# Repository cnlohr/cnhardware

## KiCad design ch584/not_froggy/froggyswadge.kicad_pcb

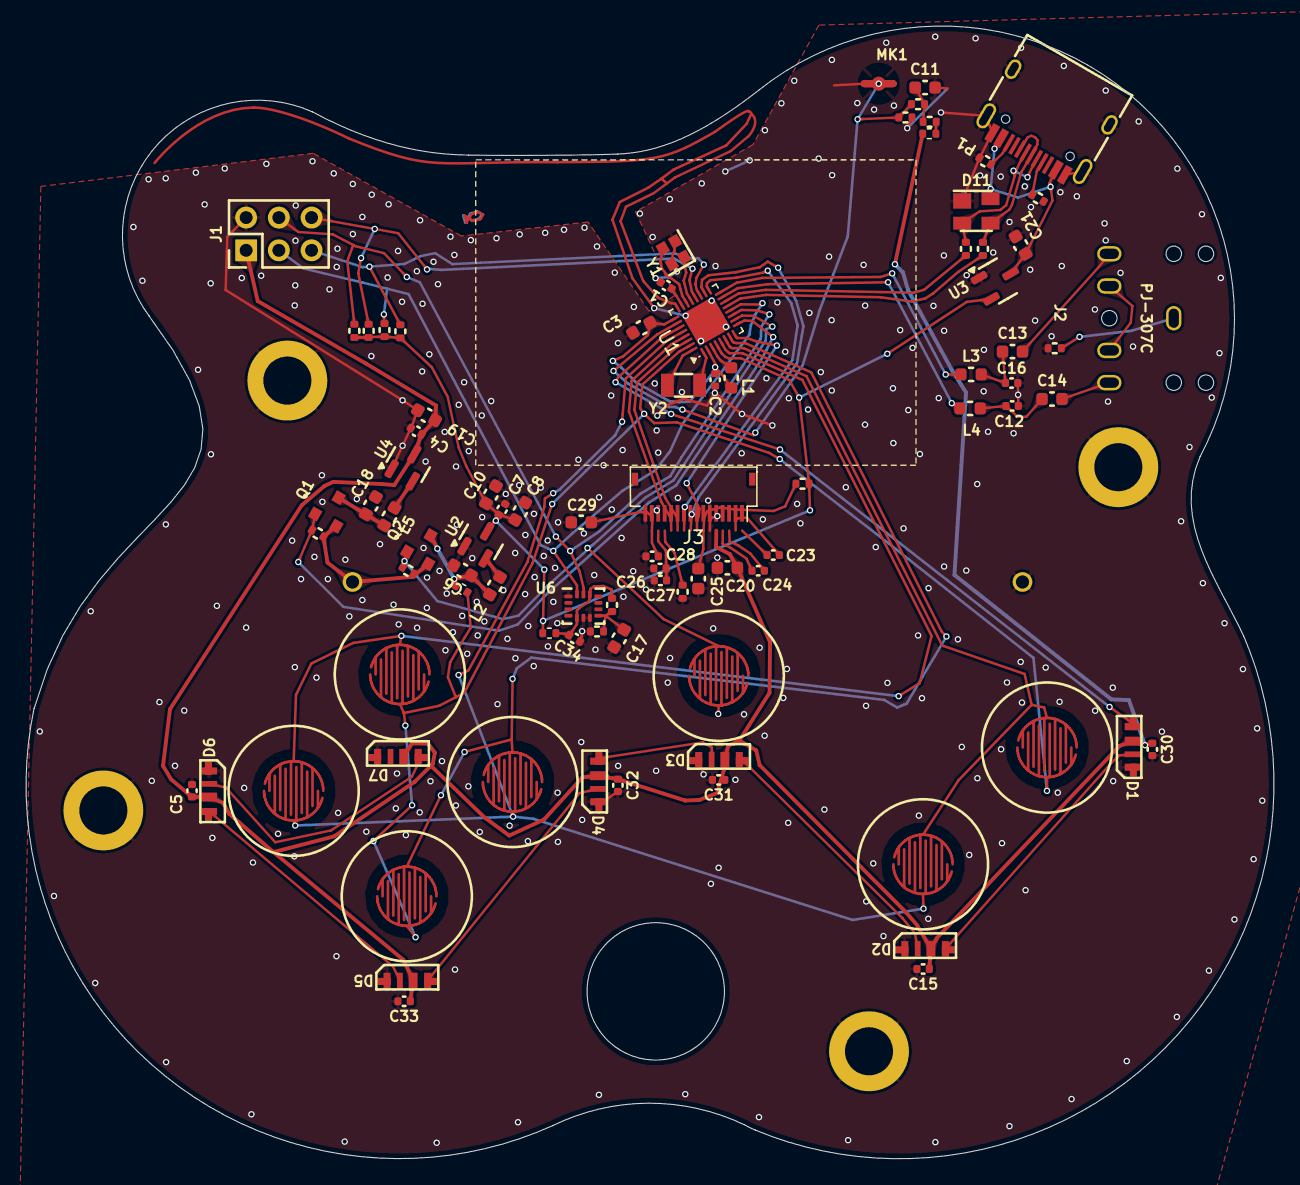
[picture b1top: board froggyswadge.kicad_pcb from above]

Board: 2 copper layers, 96.8 x 87.9 mm, 92 parts (1 on the bottom side), 66 nets.

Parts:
BT1: Battery; 2460
C1, C4, C5, C12, C15, C16, C23, C24, C26, C27, C28, C30, C31, C32, C33, C34: 1μF; C_0402_1005Metric
C2, C7: 100nF; C_0402_1005Metric
C3, C6, C8, C10, C11, C13, C14, C17, C18, C19, C20, C21, C25, C29: 10μF; C_0603_1608Metric
C9, C22: 4.7nF; R_0402_1005Metric_COMPACT
D1, D2, D3, D4, D5, D6, D7: SK6812-SIDE-A; SK6812_SIDE_2
D11: SP0503BAHT; SOT-143
J1: SAO; PinHeader_2x03_P2.54mm_Vertical
J2: PJ-307C
J3: RB130-2864KSWXG22; FPC-16-P0.50mm-HC-FPC-05-09-16RLTAG-TOP-AND-BOTTOM
J4, J5, J6, J7: MOUNT; SMTSO20xx
L1, L2, L3, L4, L5: 10uH; L_0603_1608Metric
MK1: 56db; INGHAi_MIC_GMI4013S-2C58DB
P1: USB_C_Plug_USB2.0; USB_C_Receptacle_HRO_TYPE-C-31-M-12
Q1, Q2: PMOS; SOT-23
R1, R7, R8, R11, R12, R27, R28: 5.1kΩ; R_0402_1005Metric_COMPACT
R2, R3, R6, R13, R14: 33Ω; R_0402_1005Metric_COMPACT
R4, R5: 1MΩ; R_0402_1005Metric_COMPACT
R9: IMUSHUNT; R_0402_1005Metric_COMPACT
R10, R16: 560kΩ; R_0402_1005Metric_COMPACT
R15: OLEDSHUNT; R_0402_1005Metric_COMPACT
R17: MICSHUNT; R_0402_1005Metric_COMPACT
SW1, SW2, SW3, SW4, SW5, SW6, SW7: TS-1187A-B-A-B; BTC007_Button_Silicone
U1: CH584F; VQFN-32-1EP_4x4mm_P0.4mm_EP2.8x2.8mm
U2: SM5701_2.2V; SOT-23
U3: XC6206PxxxMR; SOT-23-3
U4: XT1861B332MR-G; SOT-23
U6: LSM6DSL; LGA-14_3x2.5mm_P0.5mm_LayoutBorder3x4y
Y1: 32MHz; Crystal_SMD_2016-4Pin_2.0x1.6mm
Y2: 32.768kHz; Crystal_SMD_3215-2Pin_3.2x1.5mm

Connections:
+2V2: C7.1, C8.1, C10.1, R7.1, R8.1, R9.1, R11.1, R12.1, R15.2, U1.4 (VIO/DD33), U2.3 (OUT), U3.2 (VO)
+3V3: C4.1, C5.1, C15.1, C19.1, C20.1, C30.1, C31.1, C32.1, C33.1, D1.2 (VDD), D2.2 (VDD), D3.2 (VDD), D4.2 (VDD), D5.2 (VDD), D6.2 (VDD), D7.2 (VDD), J1.1, J3.5, R17.2, U4.3 (OUT)
AUDIOM: L4.1, U1.15 (B7)
AUDIOP: L3.1, U1.16 (B6)
B0: SW1.1 (A), SW4.1 (A), U1.5 (B9)
B1: SW2.1 (A), SW5.1 (A), U1.6 (B8)
B2: SW3.1 (A), SW6.1 (A), U1.7 (B17)
BARA: R10.1, SW1.2 (B), SW2.2 (B), SW3.2 (B), U1.31 (PA12)
BARB: SW4.2 (B), SW5.2 (B), SW6.2 (B), U1.28 (PA15)
BATT: BT1.1 (+), Q1.2 (S), Q2.2 (S), R4.1, R5.1
BATTLX22: L2.2, U2.2 (LX)
BATTLX33: L5.2, U4.2 (LX)
BATTMID22: C6.1, L2.1, Q2.3 (D), R10.2
BATTMID33: C18.1, L5.1, Q1.3 (D)
CC1: P1.A5 (CC1), R28.2
CC2: P1.B5 (CC2), R27.2
GND: BT1.2 (-), C1.2, C2.2, C3.2, C4.2, C5.2, C6.2, C7.2, C8.2, C9.1, C10.2, C11.2, C12.2, C15.2, C16.2, C17.1, C18.2, C19.2, C20.2, C21.2, C22.1, C25.2, C26.2, C27.2, C28.2, C29.2, C30.2, C31.2, C32.2, C33.2, C34.1, D1.4 (GND), D2.4 (GND), D3.4 (GND), D4.4 (GND), D5.4 (GND), D6.4 (GND), D7.4 (GND), D11.1 (A), J1.2, J3.6, J3.16, J4.1, J5.1, J6.1, J7.1, MK1.1 (-), P1.A1_B12 (GND), P1.A12_B1 (GND), P1.S1 (SHIELD), R3.2, R16.2, R27.1, R28.1, SW7.2 (B), U1.24 (ANT), U1.33 (F), U2.1 (GND), U3.1 (GND), U4.1 (GND), U6.1 (SA0), U6.6 (GND), U6.7 (GND), Y1.2, Y1.4
LED: D1.1 (IN), U1.27 (PA5)
MIC: C9.2, MK1.2 (+), R1.1, U1.26 (PA4)
unnamed: C11.1, R1.2, R2.1
unnamed: C12.1, C14.1, L4.2
unnamed: C13.1, C16.1, L3.2
unnamed: C13.2, J2.5
unnamed: C14.2, J2.2
unnamed: D1.3 (OUT), D2.1 (IN)
unnamed: D2.3 (OUT), D3.1 (IN)
unnamed: D3.3 (OUT), D4.1 (IN)
unnamed: D4.3 (OUT), D5.1 (IN)
unnamed: D5.3 (OUT), D6.1 (IN)
unnamed: D6.3 (OUT), D7.1 (IN)
unnamed: J2.1, R3.1
unnamed: J2.3, J2.4
unnamed: C23.2, J3.1
unnamed: C23.1, J3.2
unnamed: C24.2, J3.3
unnamed: C24.1, J3.4
unnamed: C25.1, J3.7, R15.1
unnamed: J3.13, R16.1
unnamed: C26.1, C27.1, J3.14
unnamed: C28.1, C29.1, J3.15
unnamed: D11.2 (K), P1.A7 (DN1), P1.B7 (DN2), R14.2
unnamed: D11.3 (K), P1.A6 (DP1), P1.B6 (DP2), R13.2
unnamed: R2.2, R17.1
unnamed: U1.1 (A10), Y2.1
unnamed: U1.32 (PA11), Y2.2
unnamed: C1.1, U1.23 (VINTA)
unnamed: L1.2, U1.3 (VSW)
unnamed: U1.22 (X32MI), Y1.3
unnamed: U1.21 (X32MO), Y1.1
unnamed: C34.2, R6.1, R9.2, U6.5 (VDDIO), U6.12 (CS)
unnamed: C17.2, C22.2, R6.2, U6.8 (VDD)
OLEDCS: J3.8, U1.8 (B16)
OLEDDC: J3.10, U1.17 (B5)
OLEDMOSI: J3.12, U1.29 (PA14)
OLEDRST: J3.9, U1.18 (B4)
OLEDSCK: J3.11, U1.30 (PA13)
PGM_TCK: Q1.1 (G), R4.2, U1.9 (B15)
PGM_TIO: Q2.1 (G), R5.2, SW7.1 (A), U1.10 (B14)
SAOG1: J1.5, R12.2, U1.19 (B23)
SAOG2: J1.6, R11.2, U1.20 (B22)
SCL_SAO: J1.4, R8.2, U1.11 (B13), U6.13 (SCL)
SDA_SAO: J1.3, R7.2, U1.12 (B12), U6.14 (SDA)
USB_D+: R13.1, U1.13 (B11)
USB_D-: R14.1, U1.14 (B10)
VBUS: C21.1, D11.4 (K), P1.A4_B9 (VBUS), P1.A9_B4 (VBUS), U3.3 (VI)
VCIA: C2.1, C3.1, L1.1, U1.2 (VDCID), U1.25 (VCIA)

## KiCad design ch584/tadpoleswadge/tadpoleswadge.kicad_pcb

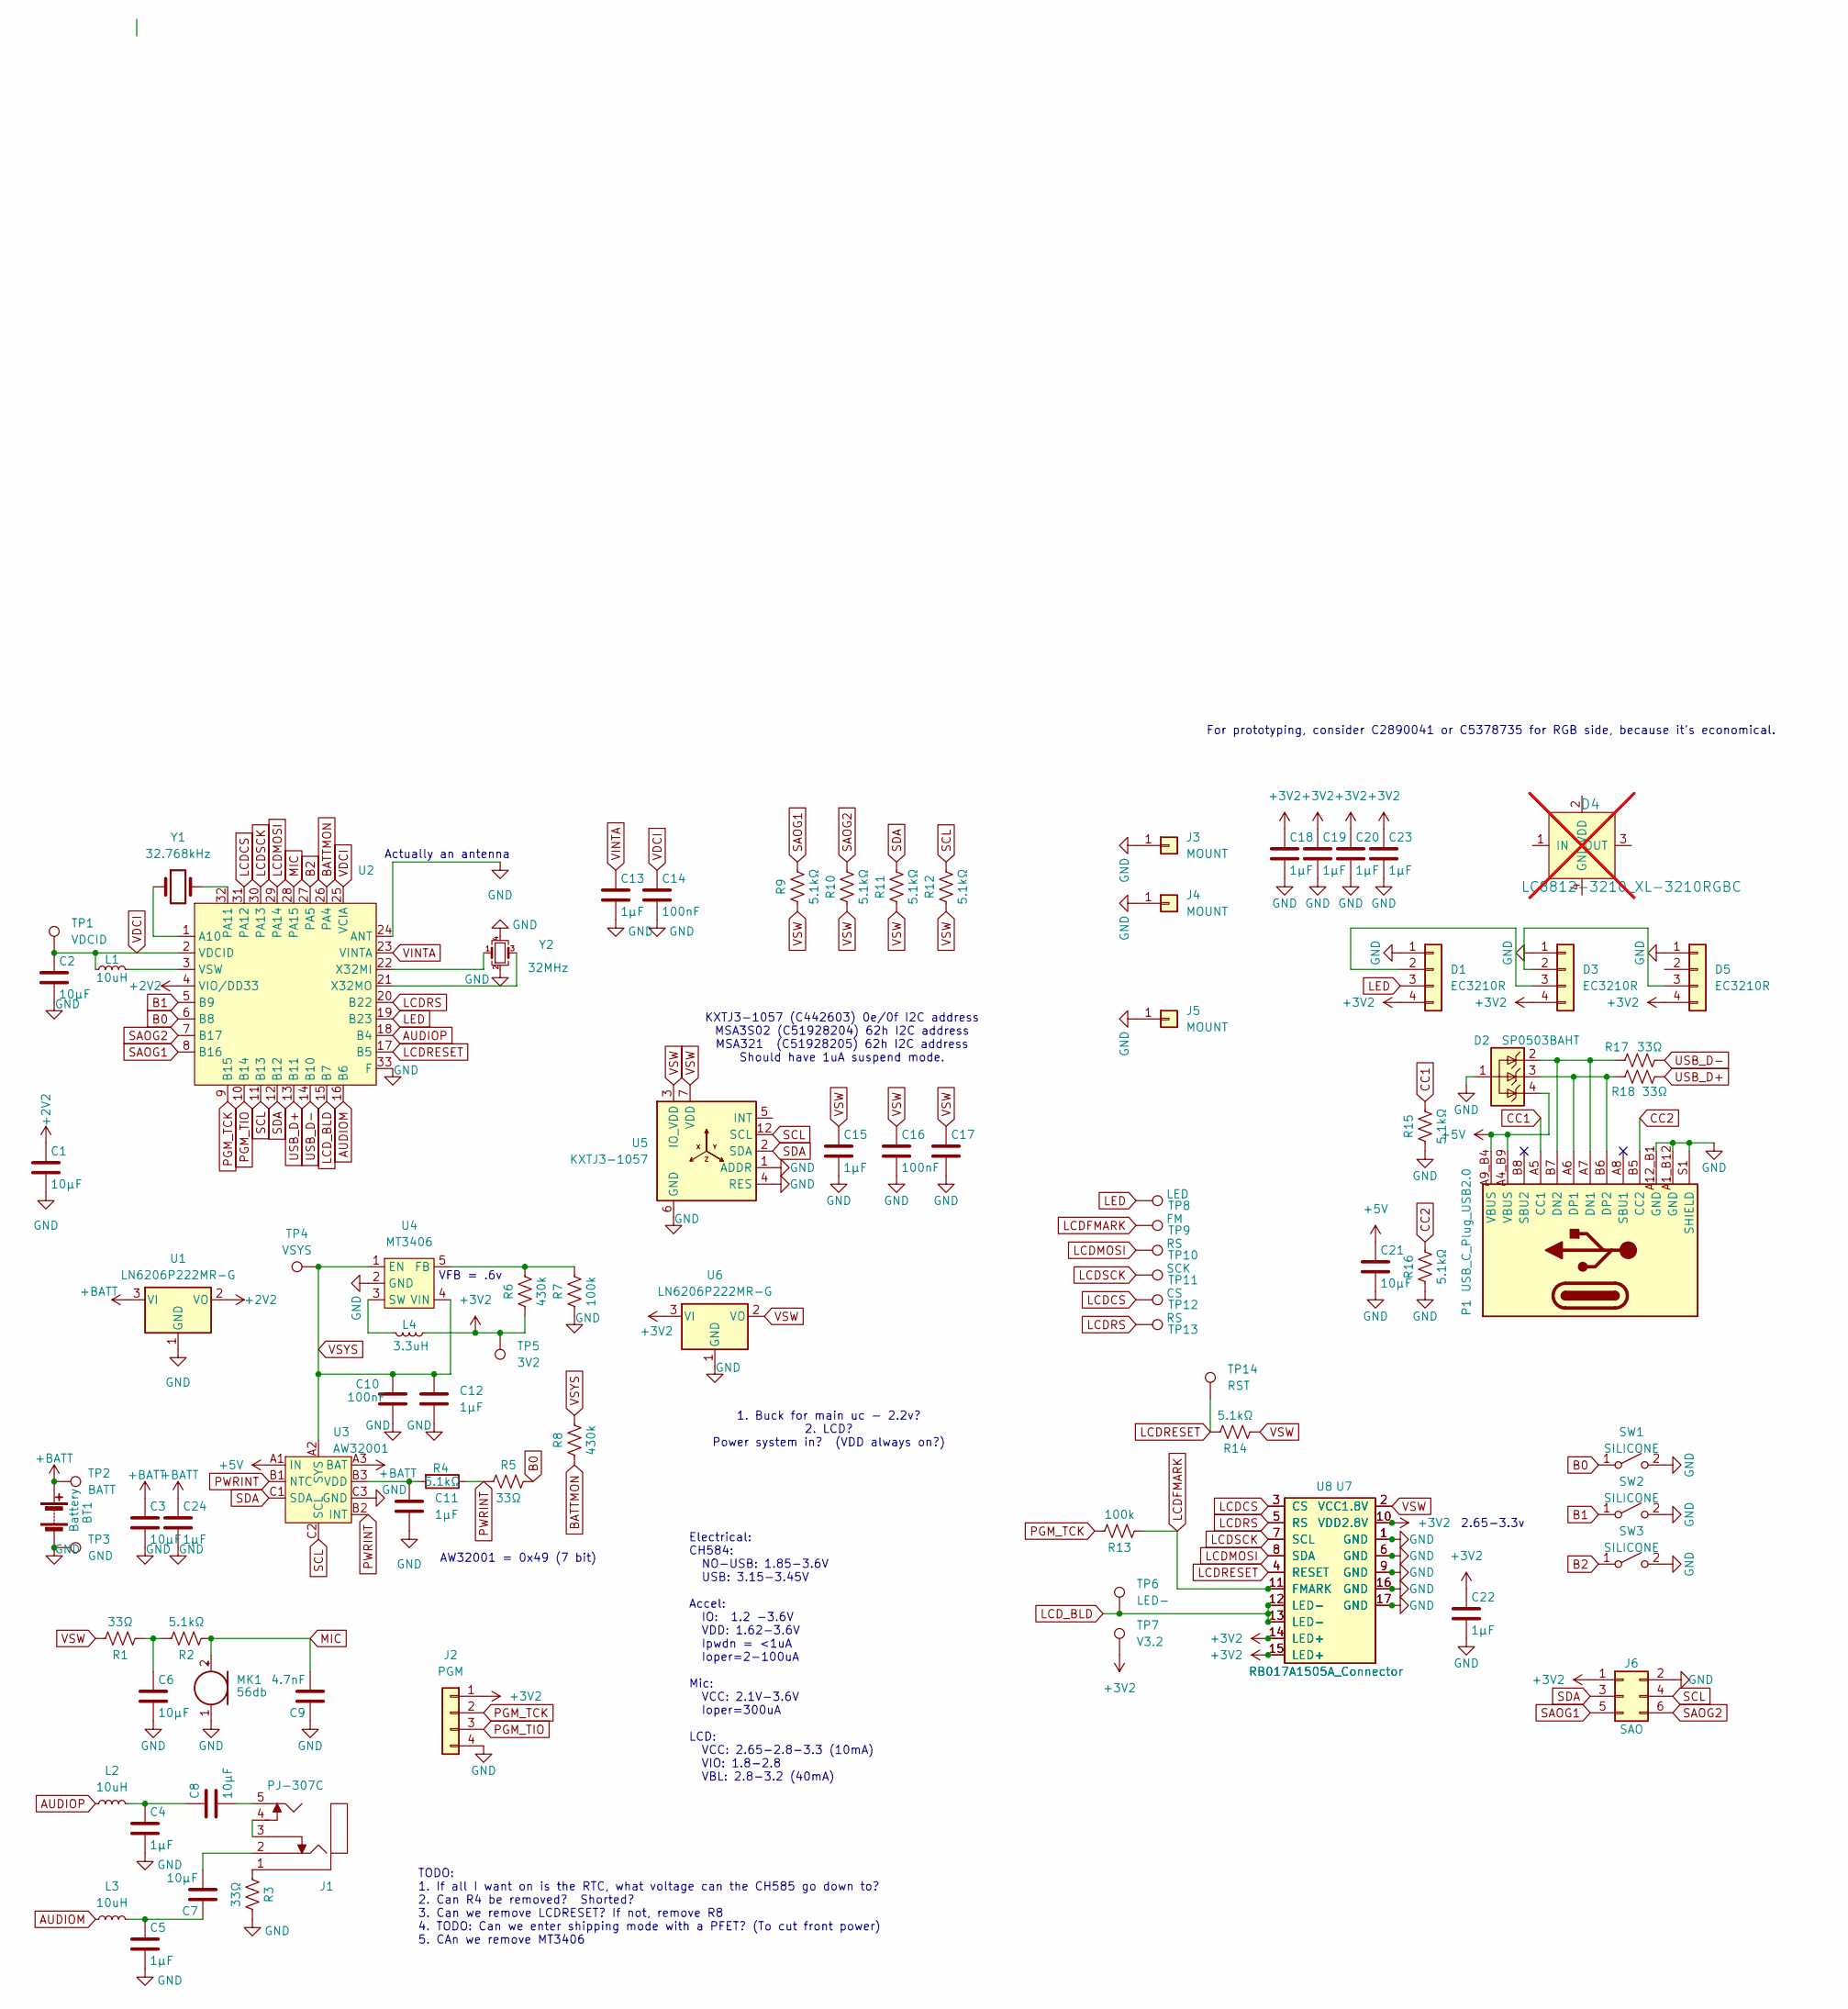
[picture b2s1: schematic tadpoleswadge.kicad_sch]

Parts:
BT1: Battery; 2460
C1, C2, C3, C6, C7, C8, C17, C21: 10μF; C_0603_1608Metric; LCSC C19702
C4, C5, C11, C12, C13, C15, C18, C19, C20, C22, C23, C24: 1μF; C_0402_1005Metric; LCSC C52923
C9: 4.7nF; R_0402_1005Metric_COMPACT; LCSC C1538
C10, C14, C16: 100nF; C_0402_1005Metric; LCSC C1525
D1, D3, D5: EC3210R; EC3210R-OPSCO-RGB-LED; LCSC C2890041
D2: SP0503BAHT; SOT-143; Digikey F2715CT-ND
D4: LC8812-3210_XL-3210RGBC; Digikey 1528-4691-ND; not fitted
J1: PJ-307C; LCSC C16684
J2: PGM; PinHeader_1x04_P2.54mm_Vertical
J3, J4, J5: MOUNT; SMTSO20xx; LCSC C2916318
J6: SAO; PinSocket_2x03_P2.54mm_Vertical; LCSC C92272
L1, L2, L3: 10uH; L_0603_1608Metric; LCSC C307750
L4: 3.3uH; L_0805_2012Metric; LCSC C394958
MK1: 56db; INGHAi_MIC_GMI4013S-2C58DB; LCSC C529869
P1: USB_C_Plug_USB2.0; USB_C_Receptacle_HRO_TYPE-C-31-M-12; LCSC C2765186
R1, R3, R5, R17, R18: 33Ω; R_0402_1005Metric_COMPACT; LCSC C25105
R2, R4, R9, R10, R11, R12, R14, R15, R16: 5.1kΩ; R_0402_1005Metric_COMPACT; LCSC C25905
R6, R8: 430k; R_0402_1005Metric_COMPACT; LCSC C25786
R7, R13: 100k; R_0402_1005Metric_COMPACT; LCSC C25741
SW1, SW2, SW3: SILICONE; BTC007_Button_Silicone
TP1: VDCID; TestPoint_Pad_D1.0mm
TP2: BATT; TestPoint_Pad_D1.0mm
TP3: GND; TestPoint_Pad_D1.0mm
TP4: VSYS; TestPoint_Pad_D1.0mm
TP5: 3V2; TestPoint_Pad_D1.0mm
TP6: LED-; TestPoint_Pad_D1.0mm
TP7: V3.2; TestPoint_Pad_D1.0mm
TP8: LED; TestPoint_Pad_D1.0mm
TP9: FM; TestPoint_Pad_D1.0mm
TP10, TP13: RS; TestPoint_Pad_D1.0mm
TP11: SCK; TestPoint_Pad_D1.0mm
TP12: CS; TestPoint_Pad_D1.0mm
TP14: RST; TestPoint_Pad_D1.0mm
U1, U6: LN6206P222MR-G; SOT-23; LCSC C3008044
U2: VQFN-32-1EP_4x4mm_P0.4mm_EP2.8x2.8mm; LCSC C42381468
U3: AW32001; WLCSP-9-P0.5mm; LCSC C5125890
U4: MT3406; SOT-23-5; LCSC C22462728
U5: KXTJ3-1057; Kionix_LGA-12_2x2mm_P0.5mm_LayoutBorder2x4y; LCSC C51928204
U7: RB017A1505A_Connector; HCTL HC-FPC-03-10-15RLTAG-TUCKED; Digikey A141392TR-ND
U8: RB017A1505A_Connector; 0.3K-HX-15PWB-LCD-CONNECTOR-TOP; LCSC C2919525
Y1: 32.768kHz; Crystal_SMD_3215-2Pin_3.2x1.5mm; LCSC C7294751
Y2: 32MHz; Crystal_SMD_2016-4Pin_2.0x1.6mm; LCSC C2965584

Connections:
+2V2: C1.1, U1.2 (VO), U2.4 (VIO/DD33)
+3V2: C18.1, C19.1, C20.1, C22.1, C23.1, D1.4, D3.4, D5.4, J2.1, J6.1, L4.1, R6.1, TP5.1, TP7.1, U6.3 (VI), U7.10 (VDD2.8V), U7.14 (LED+), U7.15 (LED+), U8.10 (VDD2.8V), U8.14 (LED+), U8.15 (LED+)
+5V: C21.1, D2.4 (K), P1.A4_B9 (VBUS), P1.A9_B4 (VBUS), U3.A1 (IN)
+BATT: BT1.1 (+), C3.1, C24.1, TP2.1, U1.3 (VI), U3.A3 (BAT)
AUDIOM: L3.1, U2.16 (B6)
AUDIOP: L2.1, U2.18 (B4)
B0: R5.2, SW1.1 (A), U2.6 (B8)
B1: SW2.1 (A), U2.5 (B9)
B2: SW3.1 (A), U2.27 (PA5)
BATTMON: R8.1, U2.26 (PA4)
CC1: P1.A5 (CC1), R15.2
CC2: P1.B5 (CC2), R16.2
GND: BT1.2 (-), C1.2, C2.2, C3.2, C4.2, C5.2, C6.2, C9.1, C10.2, C11.2, C12.2, C13.2, C14.2, C15.2, C16.2, C17.2, C18.2, C19.2, C20.2, C21.2, C22.2, C23.2, C24.2, D1.1, D2.1 (A), D3.1, D5.1, J2.4, J3.1, J4.1, J5.1, J6.2, MK1.1 (-), P1.A1_B12 (GND), P1.A12_B1 (GND), P1.S1 (SHIELD), R3.2, R7.1, R15.1, R16.1, SW1.2 (B), SW2.2 (B), SW3.2 (B), TP3.1, U1.1 (GND), U2.24 (ANT), U2.33 (F), U3.C3 (GND), U4.2 (GND), U5.1 (ADDR), U5.4 (RES), U5.6 (GND), U5.8 (GND), U5.9 (GND), U6.1 (GND), U7.1 (GND), U7.6 (GND), U7.9 (GND), U7.16 (GND), U7.17 (GND), U8.1 (GND), U8.6 (GND), U8.9 (GND), U8.16 (GND), U8.17 (GND), Y2.2, Y2.4
LCDCS: TP12.1, U2.31 (PA12), U7.3 (CS), U8.3 (CS)
LCDFMARK: R13.1, TP9.1, U7.11 (FMARK), U8.11 (FMARK)
LCDMOSI: TP10.1, U2.29 (PA14), U7.8 (SDA), U8.8 (SDA)
LCDRESET: R14.2, TP14.1, U2.17 (B5), U7.4 (RESET), U8.4 (RESET)
LCDRS: TP13.1, U2.20 (B22), U7.5 (RS), U8.5 (RS)
LCDSCK: TP11.1, U2.30 (PA13), U7.7 (SCL), U8.7 (SCL)
LCD_BLD: TP6.1, U2.15 (B7), U7.12 (LED-), U7.13 (LED-), U8.12 (LED-), U8.13 (LED-)
LED: D1.3, TP8.1, U2.19 (B23)
MIC: C9.2, MK1.2 (+), R2.1, U2.28 (PA15)
unnamed: C4.1, C8.1, L2.2
unnamed: C5.1, C7.1, L3.2
unnamed: C6.1, R1.1, R2.2
unnamed: C7.2, J1.2
unnamed: C8.2, J1.5
unnamed: D1.2, D3.3
unnamed: D3.2, D5.3
unnamed: J1.1, R3.1
unnamed: J1.3, J1.4
unnamed: D2.2 (K), P1.A7 (DN1), P1.B7 (DN2), R17.2
unnamed: D2.3 (K), P1.A6 (DP1), P1.B6 (DP2), R18.2
unnamed: U2.1 (A10), Y1.1
unnamed: U2.32 (PA11), Y1.2
unnamed: L1.2, U2.3 (VSW)
unnamed: U2.22 (X32MI), Y2.1
unnamed: U2.21 (X32MO), Y2.3
unnamed: C11.1, R4.2, U3.B3 (VDD)
unnamed: R6.2, R7.2, U4.5 (FB)
unnamed: L4.2, U4.3 (SW)
PGM_TCK: J2.2, R13.2, U2.9 (B15)
PGM_TIO: J2.3, U2.10 (B14)
PWRINT: R4.1, R5.1, U3.B1 (NTC), U3.B2 (INT)
SAOG1: J6.5, R9.2, U2.8 (B16)
SAOG2: J6.6, R10.2, U2.7 (B17)
SCL: J6.4, R12.2, U2.11 (B13), U3.C2 (SCL), U5.12 (SCL)
SDA: J6.3, R11.2, U2.12 (B12), U3.C1 (SDA), U5.2 (SDA)
USB_D+: R18.1, U2.13 (B11)
USB_D-: R17.1, U2.14 (B10)
VDCI: C2.1, C14.1, L1.1, TP1.1, U2.2 (VDCID), U2.25 (VCIA)
VINTA: C13.1, U2.23 (VINTA)
VSW: C15.1, C16.1, C17.1, R1.2, R9.1, R10.1, R11.1, R12.1, R14.1, U5.3 (IO_VDD), U5.7 (VDD), U5.10 (VDD), U5.11 (IO_VDD), U6.2 (VO), U7.2 (VCC1.8V), U8.2 (VCC1.8V)
VSYS: C10.1, C12.1, R8.2, TP4.1, U3.A2 (SYS), U4.1 (EN), U4.4 (VIN)

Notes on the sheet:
KXTJ3-1057 (C442603) 0e/0f I2C address MSA3S02 (C51928204) 62h I2C address MSA321 (C51928205) 62h I2C address Should have 1uA suspend mode.
TODO: 1. If all I want on is the RTC, what voltage can the CH585 go down to? 2. Can R4 be removed? Shorted? 3. Can we remove LCDRESET? If not, remove R8 4. TODO: Can we enter shipping mode with a PFET? (To cut front power) 5. CAn we remove MT3406
Electrical: CH584: NO-USB: 1.85-3.6V USB: 3.15-3.45V Accel: IO: 1.2 -3.6V VDD: 1.62-3.6V Ipwdn = <1uA Ioper=2-100uA Mic: VCC: 2.1V-3.6V Ioper=300uA LCD: VCC: 2.65-2.8-3.3 (10mA) VIO: 1.8-2.8 VBL: 2.8-3.2 (40mA)
AW32001 = 0x49 (7 bit)
Actually an antenna
1. Buck for main uc - 2.2v? 2. LCD? Power system in? (VDD always on?)
VFB = .6v
2.65-3.3v
For prototyping, consider C2890041 or C5378735 for RGB side, because it's economical.

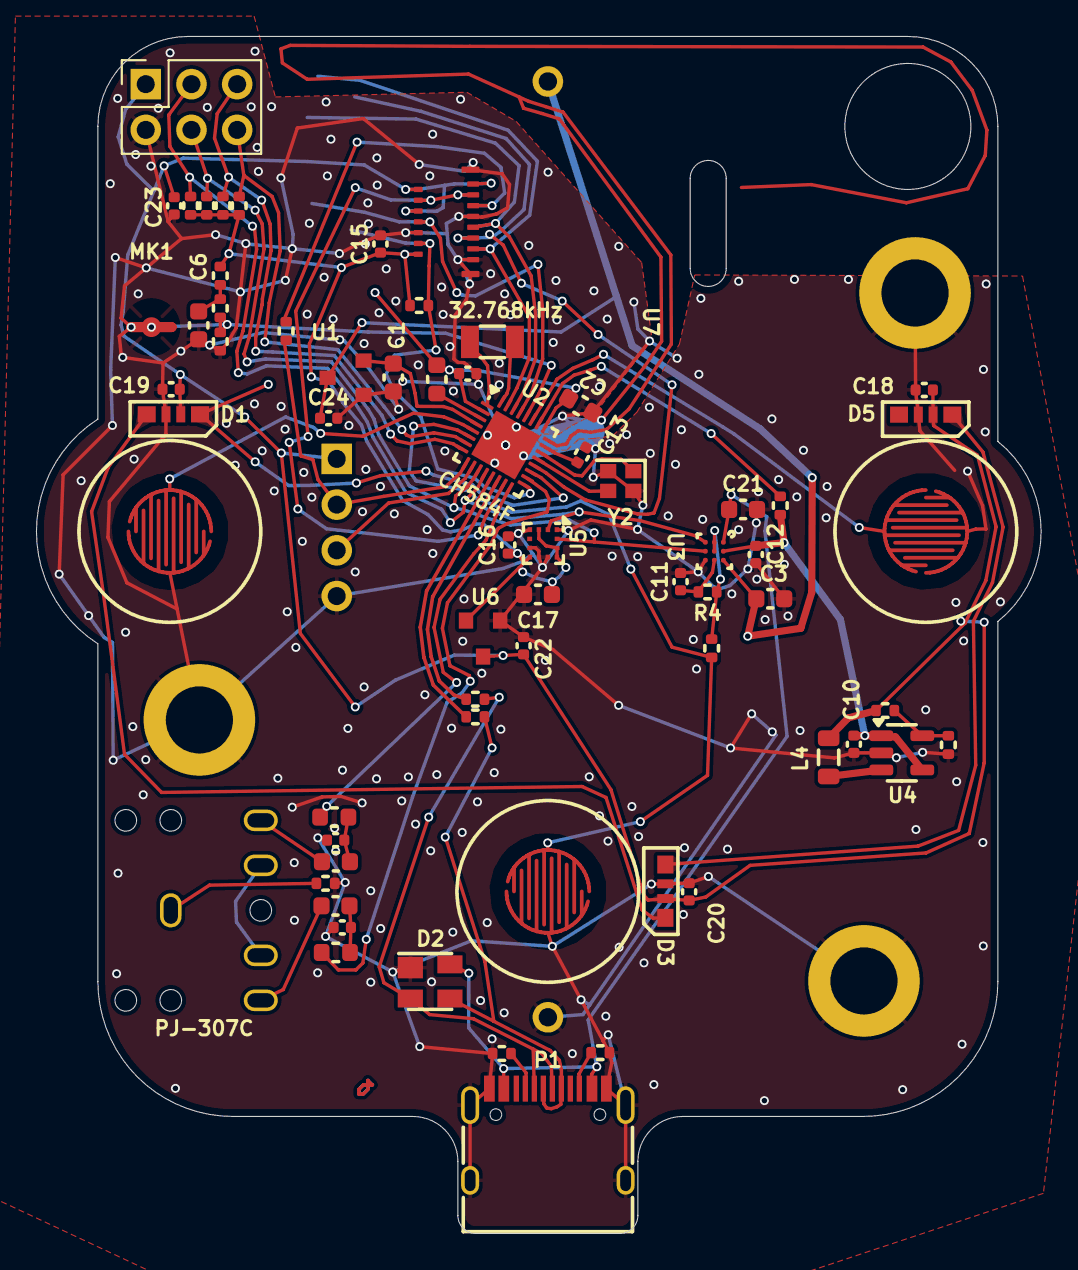
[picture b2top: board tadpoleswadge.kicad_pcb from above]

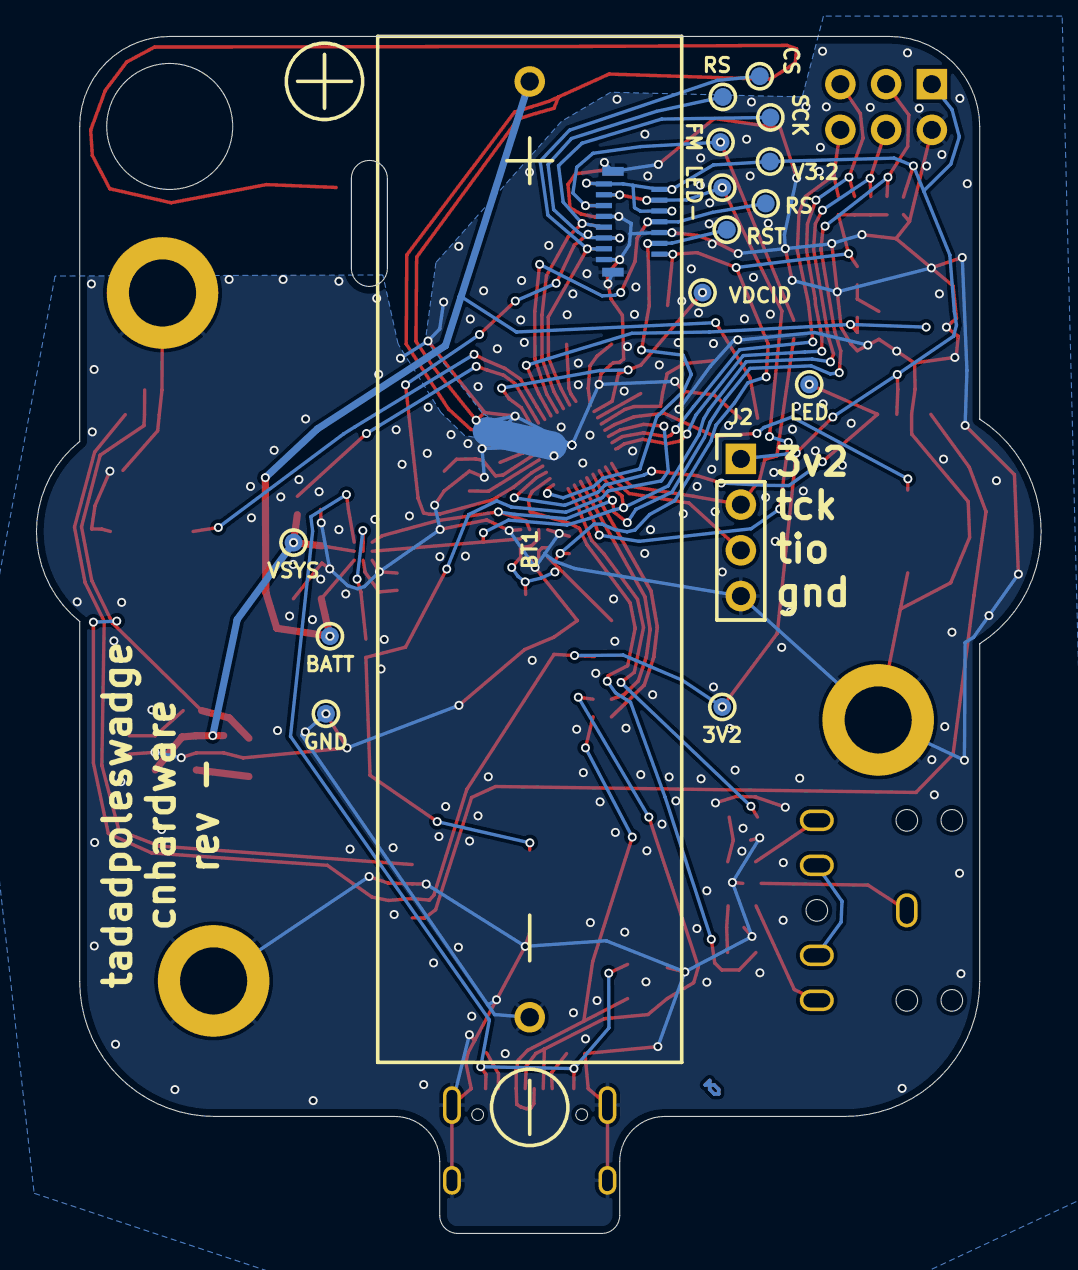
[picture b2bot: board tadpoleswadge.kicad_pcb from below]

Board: 2 copper layers, 55.8 x 66.5 mm, 86 parts (16 on the bottom side), 54 nets.
